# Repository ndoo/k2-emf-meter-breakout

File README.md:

# K-II EMF Meter Breakout Board

Work in progress.

## PCB Images

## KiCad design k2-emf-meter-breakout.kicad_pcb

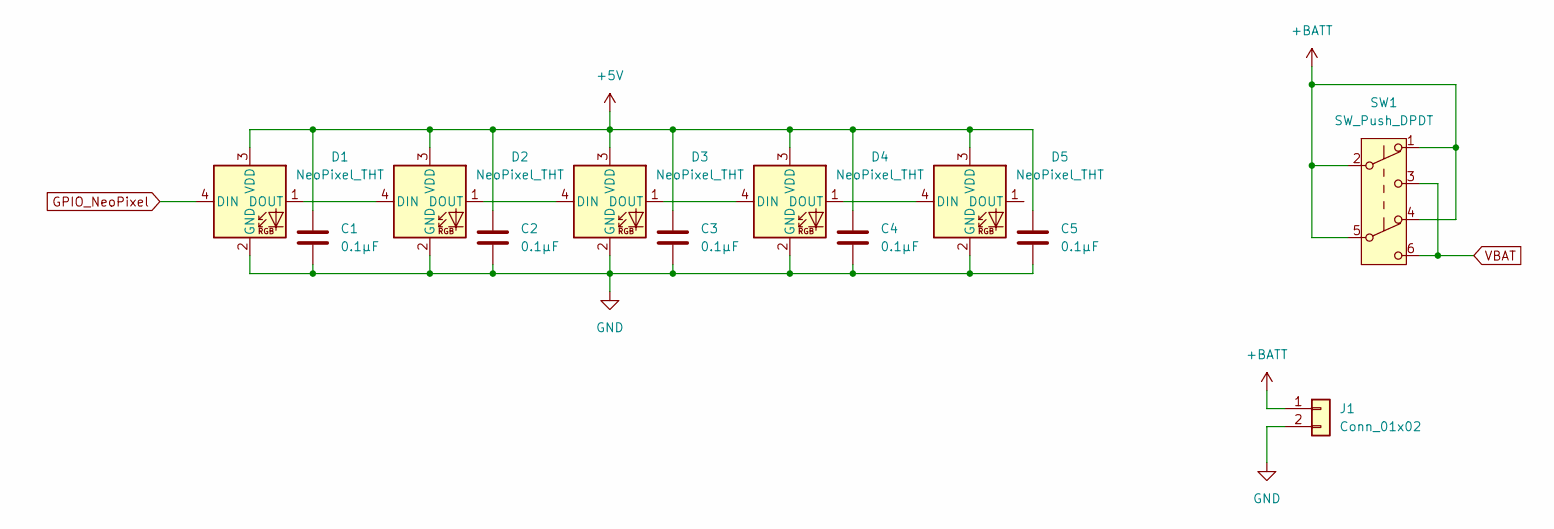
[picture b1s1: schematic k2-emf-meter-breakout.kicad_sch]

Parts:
C1, C2, C3, C4, C5: 0.1µF; C_0603_1608Metric
D1, D2, D3, D4, D5: NeoPixel_THT; LED_D5.0mm-4_RGB-Centered
J1: Conn_01x02; Molex_PicoBlade_53398-0271_1x02-1MP_P1.25mm_Vertical
SW1: SW_Push_DPDT; SW_Push_2P2T_Toggle_CK_PVA2OAH5xxxxxxV2

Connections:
+5V: C1.1, C2.1, C3.1, C4.1, C5.1, D1.3 (VDD), D2.3 (VDD), D3.3 (VDD), D4.3 (VDD), D5.3 (VDD)
+BATT: J1.1, SW1.1 (A), SW1.2 (B), SW1.4 (A), SW1.5 (B)
GND: C1.2, C2.2, C3.2, C4.2, C5.2, D1.2 (GND), D2.2 (GND), D3.2 (GND), D4.2 (GND), D5.2 (GND), J1.2
GPIO_NeoPixel: D1.4 (DIN)
unnamed: D1.1 (DOUT), D2.4 (DIN)
unnamed: D2.1 (DOUT), D3.4 (DIN)
unnamed: D3.1 (DOUT), D4.4 (DIN)
unnamed: D4.1 (DOUT), D5.4 (DIN)
VBAT: SW1.3 (C), SW1.6 (C)

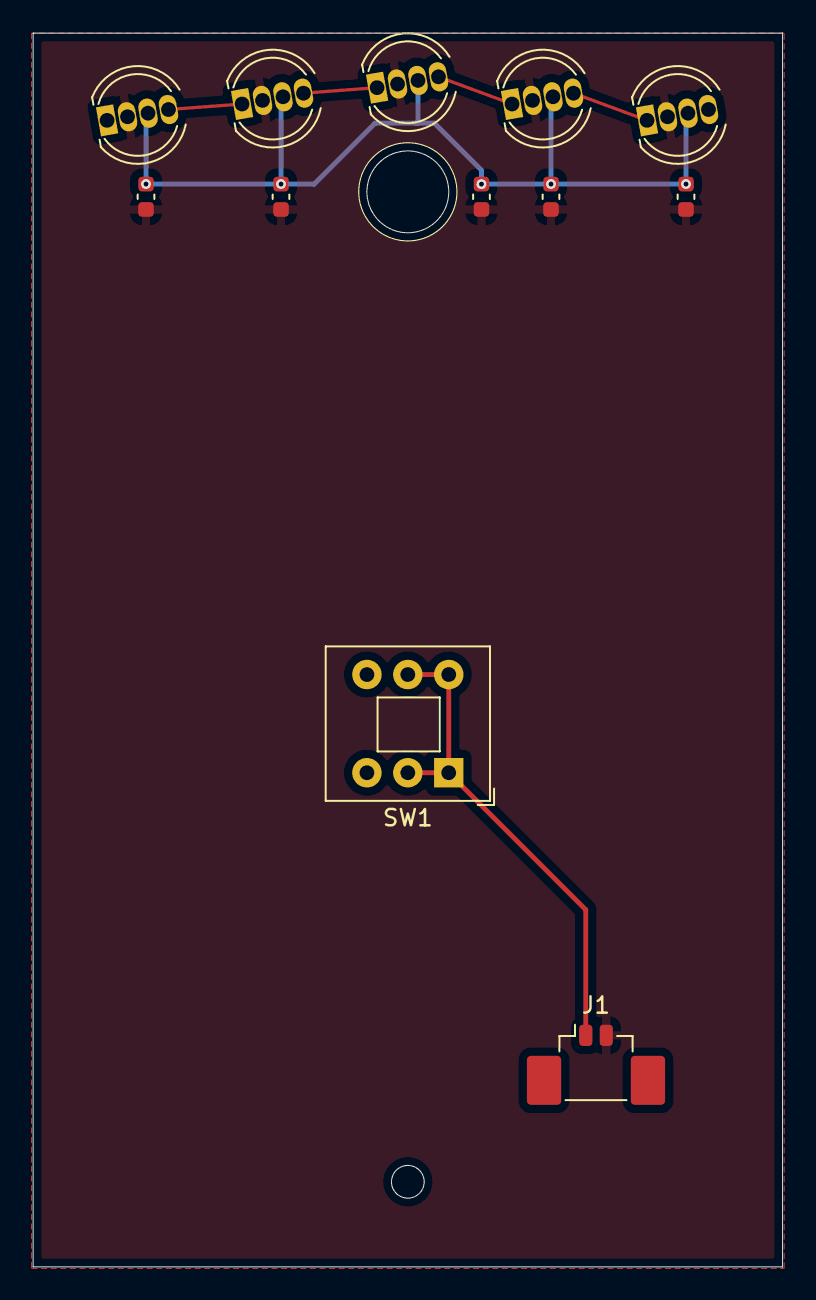
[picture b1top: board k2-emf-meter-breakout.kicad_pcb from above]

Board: 2 copper layers, 45.8 x 75.4 mm, 12 parts (0 on the bottom side), 8 nets.

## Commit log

2024-06-21 Initial layout
